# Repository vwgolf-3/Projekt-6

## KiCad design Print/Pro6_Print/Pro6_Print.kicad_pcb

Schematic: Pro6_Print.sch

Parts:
H1, H2, H3, H4: MountingHole_Pad; MountingHole_5.3mm_M5_DIN965_Pad

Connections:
GND: H1.1, H2.1, H3.1, H4.1; also elsewhere on the board

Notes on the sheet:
Motor etc
Endschalter
ESP32
RFID
Pumpen
Speisungen
Mikrocontroller
Durchflusssensoren
LED

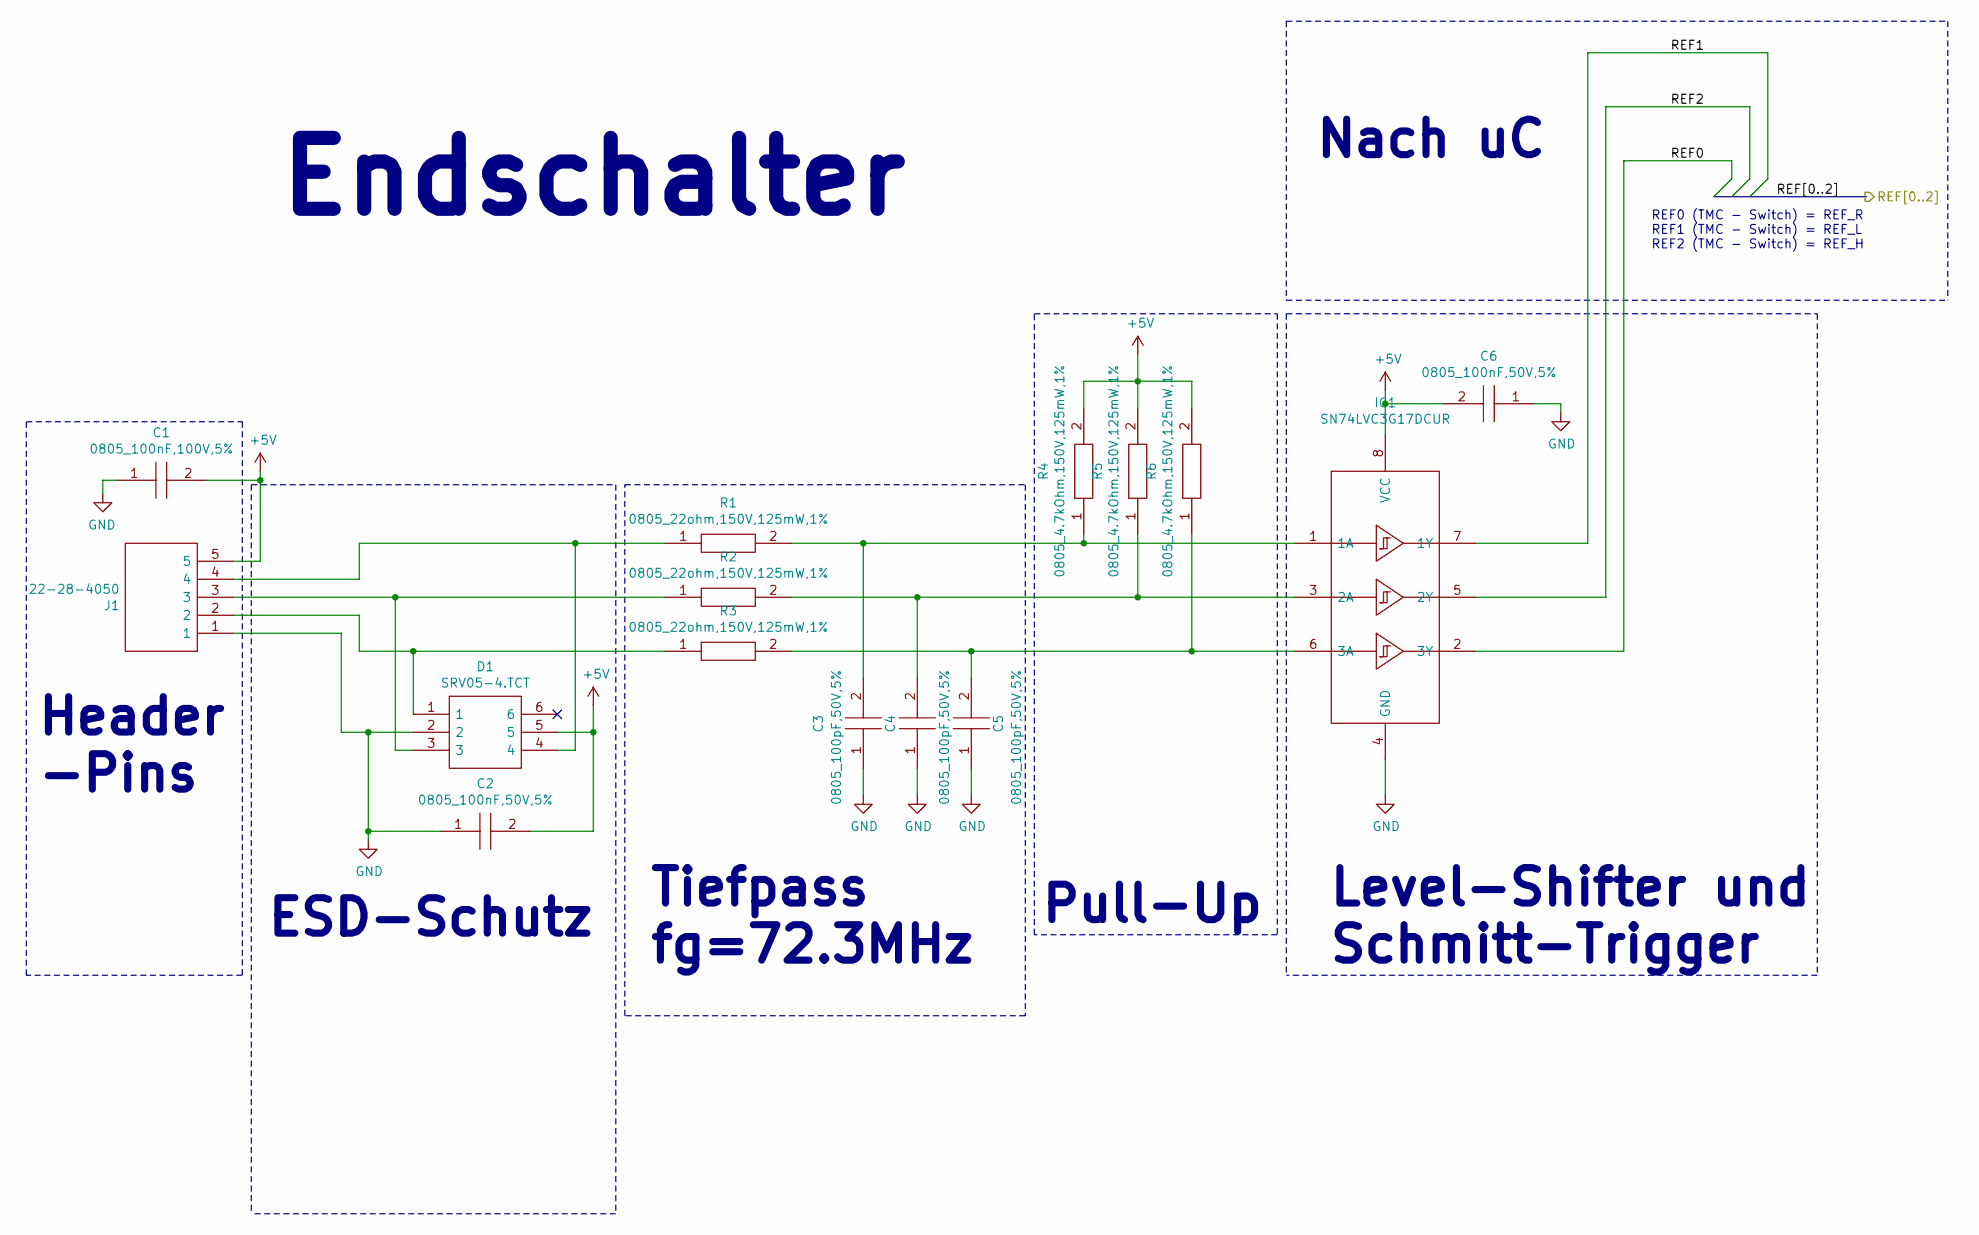
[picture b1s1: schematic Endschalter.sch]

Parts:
C1: 0805_100nF,100V,5%; CAPC2012X140N; Mouser Part Number 581-08051C104JAT2A
C2, C6: 0805_100nF,50V,5%; CAPC2012X88N; Mouser Part Number 80-C0805C104J5R
C3, C4, C5: 0805_100pF,50V,5%; CAPC2013X70N; Mouser Part Number 603-CC805JRNPO9BN101
D1: SRV05-4.TCT; SOT95P280X145-6N; Mouser Part Number 947-SRV05-4.TCT
IC1: SN74LVC3G17DCUR; SOP50P310X90-8N; Mouser Part Number 595-SN74LVC3G17DCUR
J1: 22-28-4050; HDRV5W66P0X254_1X5_1270X249X838P; Mouser Part Number 538-22-28-4050
R1, R2, R3: 0805_22ohm,150V,125mW,1%; RESC2012X70N; Mouser Part Number 667-ERJ-6ENF22R0V
R4, R5, R6: 0805_4.7kOhm,150V,125mW,1%; RESC2012X70N; Mouser Part Number 667-ERJ-6ENF4701V

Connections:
+5V: C1.2, C2.2, C6.2, D1.5, IC1.8 (VCC), J1.5, R4.2, R5.2, R6.2; also elsewhere on the board
/Atmega2560/REF0: IC1.2 (3Y); also elsewhere on the board
/Atmega2560/REF1: IC1.7 (1Y); also elsewhere on the board
/Atmega2560/REF2: IC1.5 (2Y); also elsewhere on the board
GND: C1.1, C2.1, C3.1, C4.1, C5.1, C6.1, D1.2, IC1.4 (GND), J1.1; also elsewhere on the board
unnamed: C3.2, IC1.1 (1A), R1.2, R4.1
unnamed: C4.2, IC1.3 (2A), R2.2, R5.1
unnamed: C5.2, IC1.6 (3A), R3.2, R6.1
unnamed: D1.1, J1.2, R3.1
unnamed: D1.3, J1.3, R2.1
unnamed: D1.4, J1.4, R1.1

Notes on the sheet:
Endschalter
REF0 (TMC - Switch) = REF_R REF1 (TMC - Switch) = REF_L REF2 (TMC - Switch) = REF_H
ESD-Schutz
Tiefpass fg=72.3MHz
Pull-Up
Level-Shifter und Schmitt-Trigger
Nach uC
Header -Pins

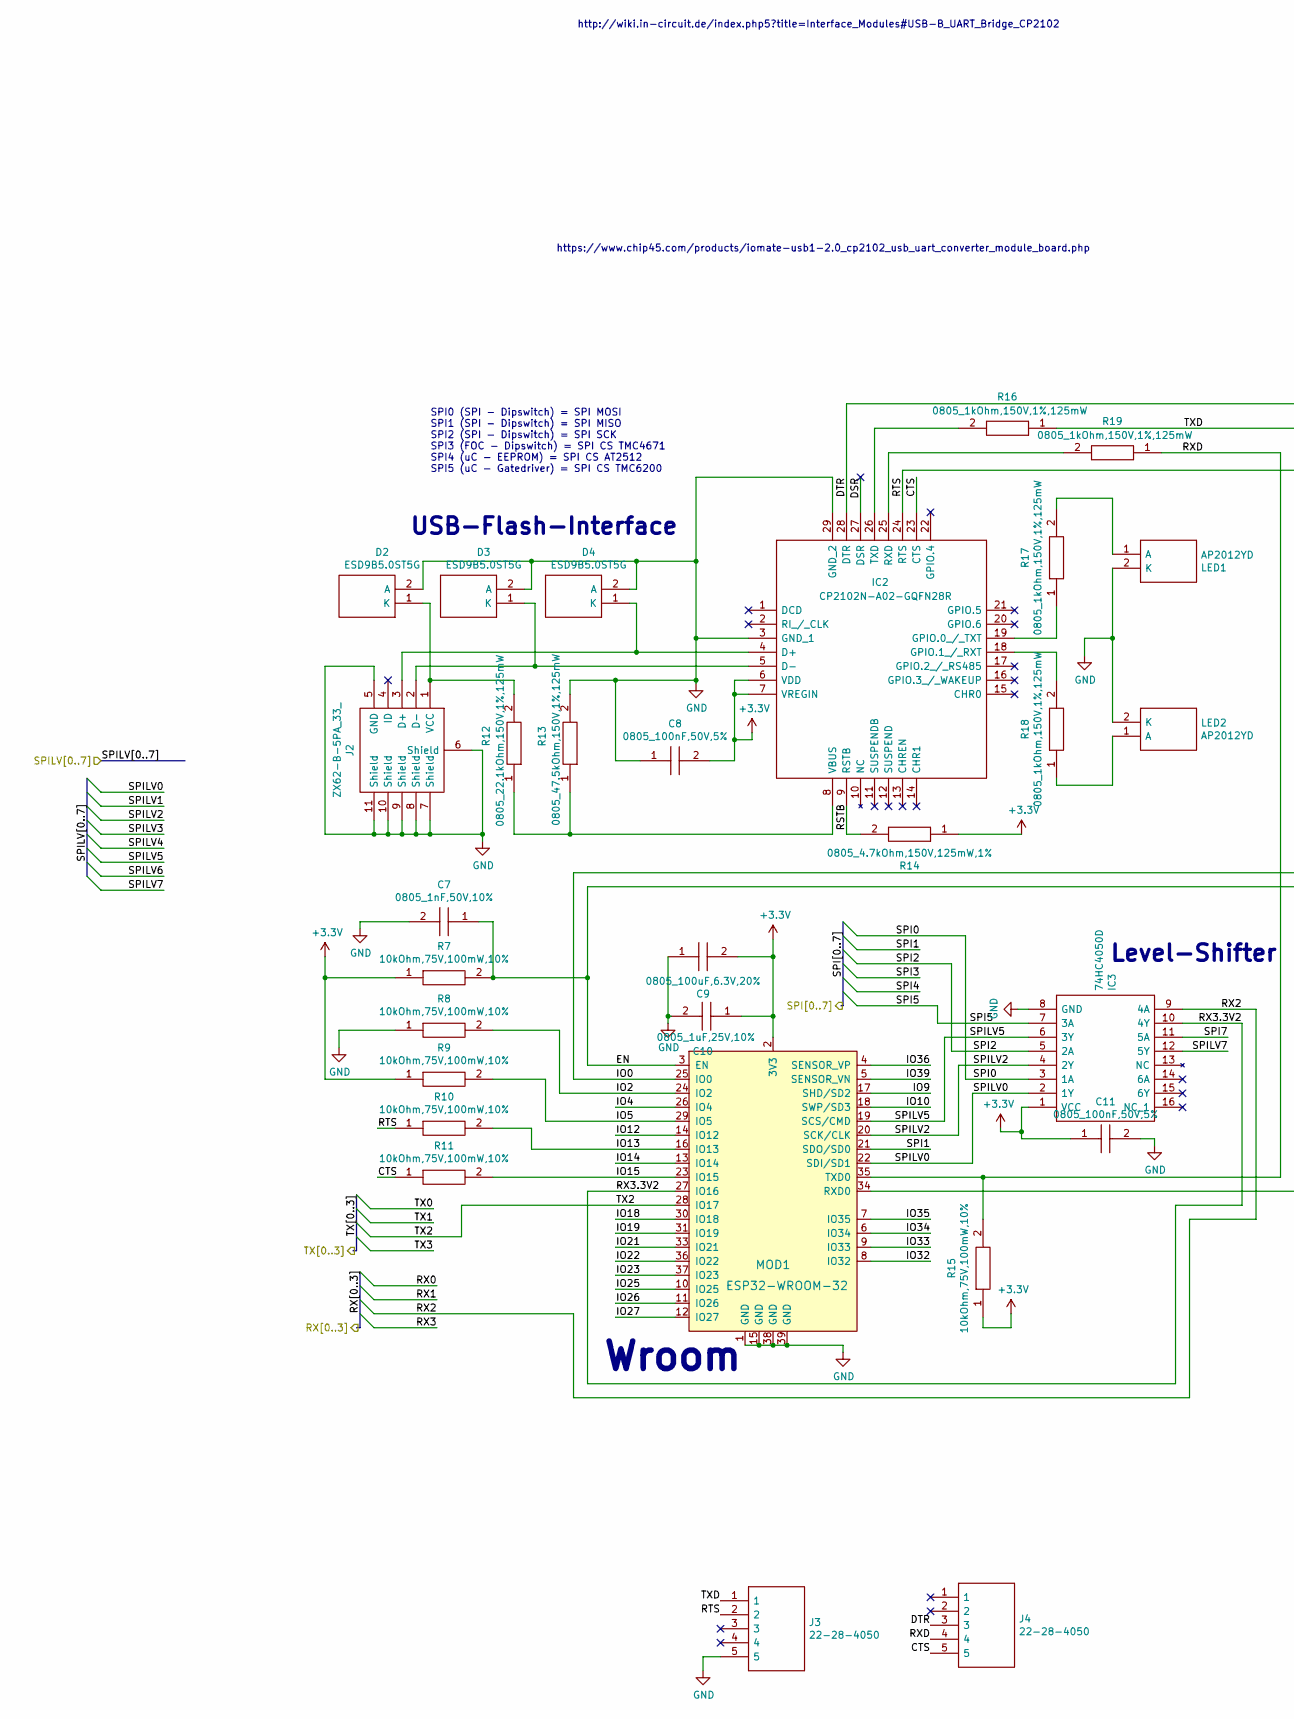
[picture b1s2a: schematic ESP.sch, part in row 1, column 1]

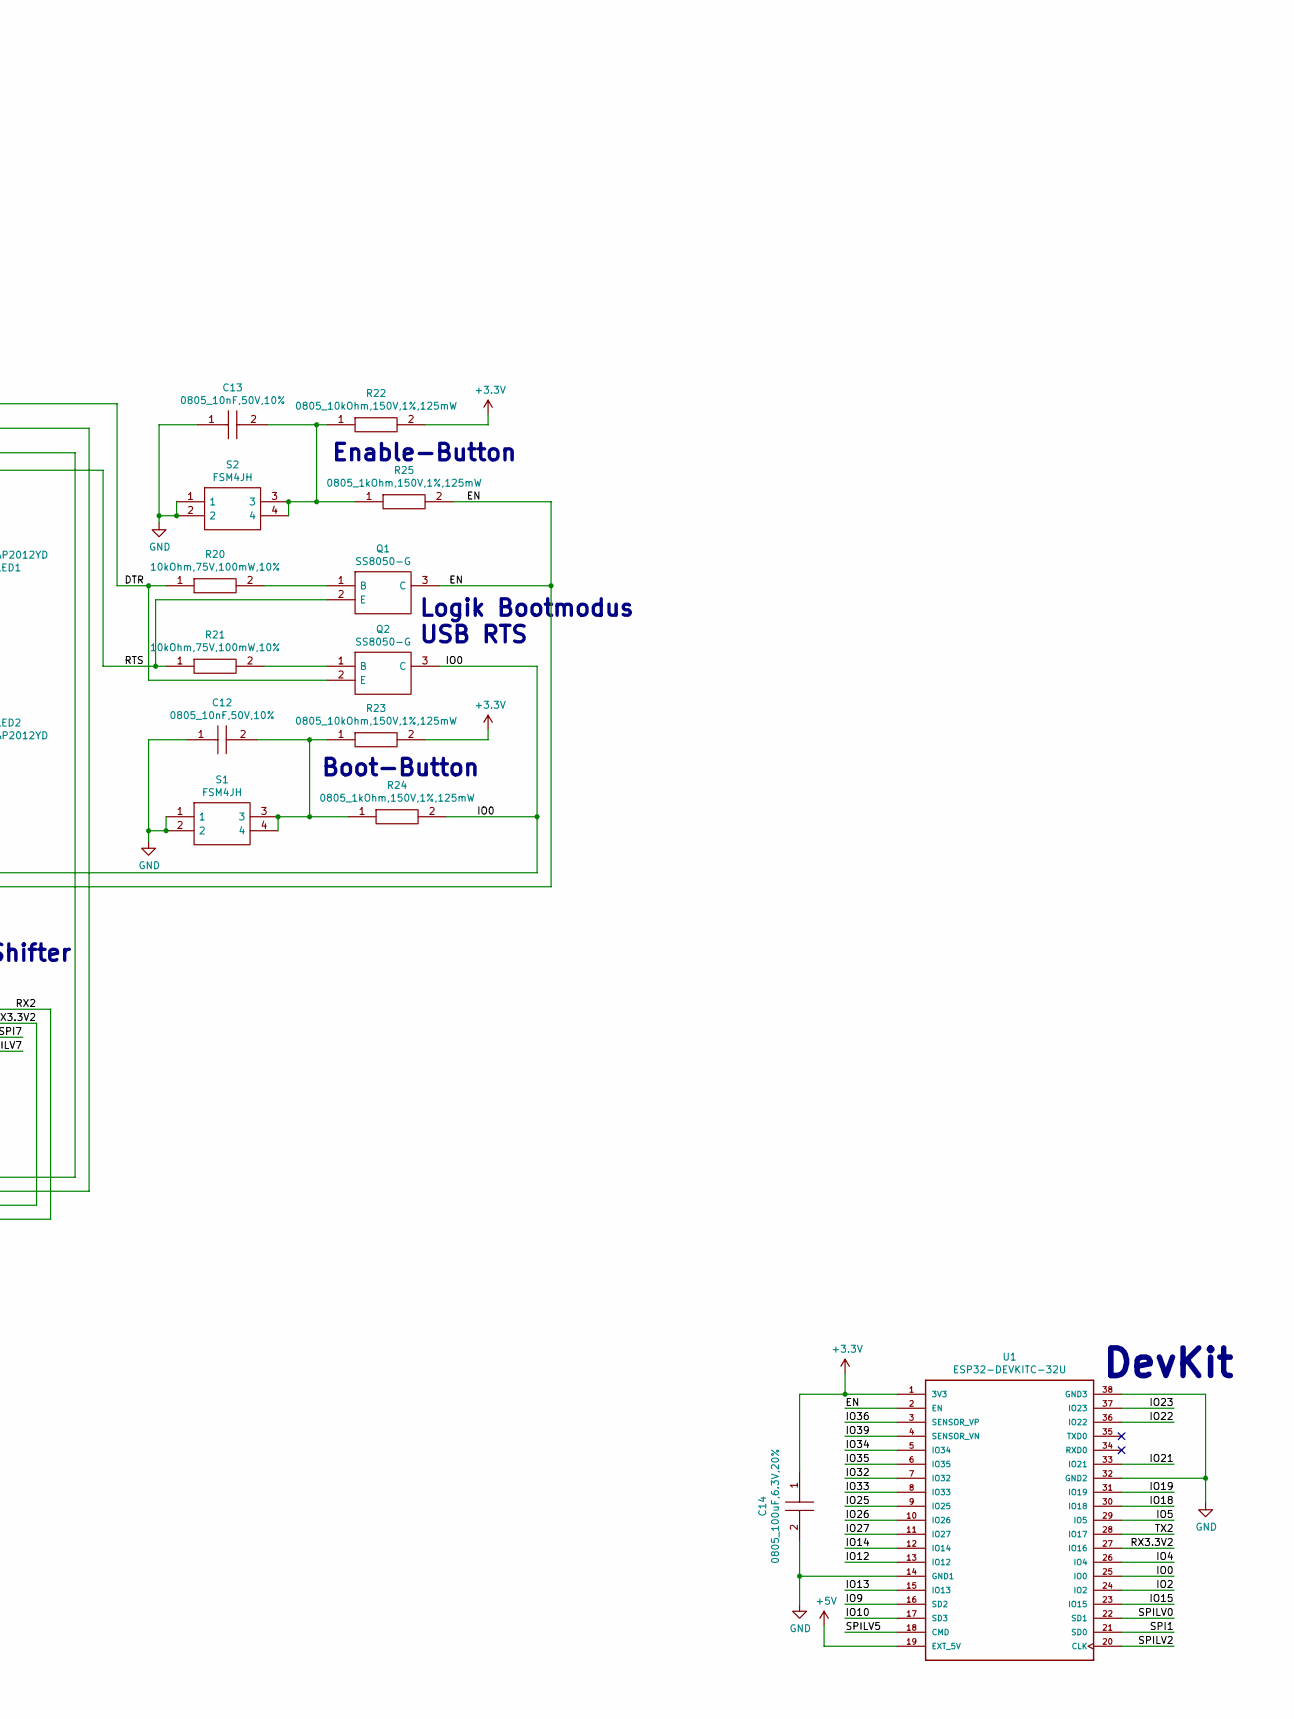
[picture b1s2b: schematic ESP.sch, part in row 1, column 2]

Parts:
C7: 0805_1nF,50V,10%; CAPC2012X90N; Mouser Part Number 710-885012207086
C8, C11: 0805_100nF,50V,5%; CAPC2012X88N; Mouser Part Number 80-C0805C104J5R
C9, C14: 0805_100uF,6.3V,20%; CAPC2012X145N; Mouser Part Number 81-GRM21BR60J107ME5K
C10: 0805_1uF,25V,10%; CAPC2013X140N; Mouser Part Number 80-C0805C105K3R
C12, C13: 0805_10nF,50V,10%; CAPC2012X90N; Mouser Part Number 710-885012207092
D2, D3, D4: ESD9B5.0ST5G; SODFL1006X40N; Mouser Part Number 863-ESD9B5.0ST5G
IC2: CP2102N-A02-GQFN28R; QFN50P500X500X80-29N-D; Mouser Part Number 634-CP2102NA02QFN28R
IC3: 74HC4050D; SOIC127P600X175-16N; Mouser Part Number 771-74HC4050D
J2: ZX62-B-5PA_33_; ZX62B5PA33; Mouser Part Number 798-ZX62-B-5PA33
J3, J4: 22-28-4050; HDRV5W66P0X254_1X5_1270X249X838P; Mouser Part Number 538-22-28-4050
LED1, LED2: AP2012YD; Mouser Part Number 604-AP2012YD
MOD1: ESP32-WROOM-32; ESP32-WROOM-32D; MPN ESP32-WROOM-32; Digi-Key_PN 1904-1010-1-ND
Q1, Q2: SS8050-G; SOT95P240X115-3N; Mouser Part Number 750-SS8050-G
R7, R8, R9, R10, R11, R15, R20, R21: 10kOhm,75V,100mW,10%; RESC1608X50N; Mouser Part Number 71-CRCW0603-10K-E3
R12: 0805_22.1kOhm,150V,1%,125mW; RESC2012X70N; Mouser Part Number 667-ERJ-6ENF2212V
R13: 0805_47.5kOhm,150V,1%,125mW; RESC2012X50N; Mouser Part Number 71-CRCW0805-47.5K-E3
R14: 0805_4.7kOhm,150V,125mW,1%; RESC2012X70N; Mouser Part Number 667-ERJ-6ENF4701V
R16, R17, R18, R19, R24, R25: 0805_1kOhm,150V,1%,125mW; RESC2012X60N; Mouser Part Number 71-CRCW08051K00FKEAC
R22, R23: 0805_10kOhm,150V,1%,125mW; RESC2012X60N; Mouser Part Number 71-CRCW080510K0FKEAC
S1, S2: FSM4JH; Mouser Part Number 506-FSM4JH
U1: ESP32-DEVKITC-32U; MODULE_ESP32-DEVKITC-32U

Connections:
+3V3: C8.2, C9.2, C10.1, C11.1, C14.1, IC2.6 (VDD), IC2.7 (VREGIN), IC3.1 (VCC), MOD1.2 (3V3), R7.1, R9.1, R14.1, R15.1, R22.2, R23.2, U1.1 (3V3); also elsewhere on the board
+5V: U1.19 (EXT_5V); also elsewhere on the board
/Atmega2560/RX2: IC3.9 (4A); also elsewhere on the board
/Atmega2560/SPI0: IC3.3 (1A); also elsewhere on the board
/Atmega2560/SPI1: MOD1.21 (SDO/SD0), U1.21 (SD0); also elsewhere on the board
/Atmega2560/SPI2: IC3.5 (2A); also elsewhere on the board
/Atmega2560/SPI5: IC3.7 (3A); also elsewhere on the board
/Atmega2560/SPI7: IC3.11 (5A); also elsewhere on the board
/Atmega2560/SPILV0: IC3.2 (1Y), MOD1.22 (SDI/SD1), U1.22 (SD1); also elsewhere on the board
/Atmega2560/SPILV2: IC3.4 (2Y), MOD1.20 (SCK/CLK), U1.20 (CLK); also elsewhere on the board
/Atmega2560/SPILV5: IC3.6 (3Y), MOD1.19 (SCS/CMD), U1.18 (CMD)
/Atmega2560/SPILV7: IC3.12 (5Y); also elsewhere on the board
/Atmega2560/TX2: MOD1.28 (IO17), U1.28 (IO17); also elsewhere on the board
/ESP/CTS: IC2.23 (CTS), J4.5, R11.1
/ESP/DTR: IC2.28 (DTR), J4.3, Q2.2 (E), R20.1
/ESP/EN: C7.1, MOD1.3 (EN), Q1.3 (C), R7.2, R25.2, U1.2 (EN)
/ESP/IO0: MOD1.25 (IO0), Q2.3 (C), R24.2, U1.25 (IO0)
/ESP/IO2: MOD1.24 (IO2), R8.2, U1.24 (IO2)
/ESP/IO4: MOD1.26 (IO4), U1.26 (IO4)
/ESP/IO5: MOD1.29 (IO5), R9.2, U1.29 (IO5)
/ESP/IO9: MOD1.17 (SHD/SD2), U1.16 (SD2)
/ESP/IO10: MOD1.18 (SWP/SD3), U1.17 (SD3)
/ESP/IO12: MOD1.14 (IO12), U1.13 (IO12)
/ESP/IO13: MOD1.16 (IO13), R10.2, U1.15 (IO13)
/ESP/IO14: MOD1.13 (IO14), U1.12 (IO14)
/ESP/IO15: MOD1.23 (IO15), R11.2, U1.23 (IO15)
/ESP/IO18: MOD1.30 (IO18), U1.30 (IO18)
/ESP/IO19: MOD1.31 (IO19), U1.31 (IO19)
/ESP/IO21: MOD1.33 (IO21), U1.33 (IO21)
/ESP/IO22: MOD1.36 (IO22), U1.36 (IO22)
/ESP/IO23: MOD1.37 (IO23), U1.37 (IO23)
/ESP/IO25: MOD1.10 (IO25), U1.9 (IO25)
/ESP/IO26: MOD1.11 (IO26), U1.10 (IO26)
/ESP/IO27: MOD1.12 (IO27), U1.11 (IO27)
/ESP/IO32: MOD1.8 (IO32), U1.7 (IO32)
/ESP/IO33: MOD1.9 (IO33), U1.8 (IO33)
/ESP/IO34: MOD1.6 (IO34), U1.5 (IO34)
/ESP/IO35: MOD1.7 (IO35), U1.6 (IO35)
/ESP/IO36: MOD1.4 (SENSOR_VP), U1.3 (SENSOR_VP)
/ESP/IO39: MOD1.5 (SENSOR_VN), U1.4 (SENSOR_VN)
/ESP/RSTB: IC2.9 (RSTB), R14.2
/ESP/RTS: IC2.24 (RTS), J3.2, Q1.2 (E), R10.1, R21.1
/ESP/RX3.3V2: IC3.10 (4Y), MOD1.27 (IO16), U1.27 (IO16)
/ESP/RXD: J4.4, MOD1.35 (TXD0), R15.2, R19.1
/ESP/TXD: J3.1, MOD1.34 (RXD0), R16.1
GND: C7.2, C8.1, C9.1, C10.2, C11.2, C12.1, C13.1, C14.2, D2.2 (A), D3.2 (A), D4.2 (A), IC2.3 (GND_1), IC2.29 (GND_2), IC3.8 (GND), J2.5 (GND), J2.6 (Shield), J2.7 (Shield), J2.8 (Shield), J2.9 (Shield), J2.10 (Shield), J2.11 (Shield), J3.5, LED1.2 (K), LED2.2 (K), MOD1.1 (GND), MOD1.15 (GND), MOD1.38 (GND), MOD1.39 (GND), R8.1, R13.2, S1.1, S1.2, S2.1, S2.2, U1.14 (GND1), U1.32 (GND2), U1.38 (GND3); also elsewhere on the board
unnamed: C12.2, R23.1, R24.1, S1.3, S1.4
unnamed: C13.2, R22.1, R25.1, S2.3, S2.4
unnamed: D2.1 (K), J2.1 (VCC), R12.2
unnamed: D3.1 (K), IC2.5 (D-), J2.2 (D-)
unnamed: D4.1 (K), IC2.4 (D+), J2.3 (D+)
unnamed: IC2.8 (VBUS), R12.1, R13.1
unnamed: IC2.18 (GPIO.1_/_RXT), R18.2
unnamed: IC2.19 (GPIO.0_/_TXT), R17.1
unnamed: IC2.25 (RXD), R19.2
unnamed: IC2.26 (TXD), R16.2
unnamed: LED1.1 (A), R17.2
unnamed: LED2.1 (A), R18.1
unnamed: Q1.1 (B), R20.2
unnamed: Q2.1 (B), R21.2

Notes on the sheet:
USB-Flash-Interface
SPI0 (SPI - Dipswitch) = SPI MOSI SPI1 (SPI - Dipswitch) = SPI MISO SPI2 (SPI - Dipswitch) = SPI SCK SPI3 (FOC - Dipswitch) = SPI CS TMC4671 SPI4 (uC - EEPROM) = SPI CS AT2512 SPI5 (uC - Gatedriver) = SPI CS TMC6200
Enable-Button
Boot-Button
Logik Bootmodus USB RTS
Level-Shifter
Wroom
DevKit
https://www.chip45.com/products/iomate-usb1-2.0_cp2102_usb_uart_converter_module_board.php
http://wiki.in-circuit.de/index.php5?title=Interface_Modules#USB-B_UART_Bridge_CP2102

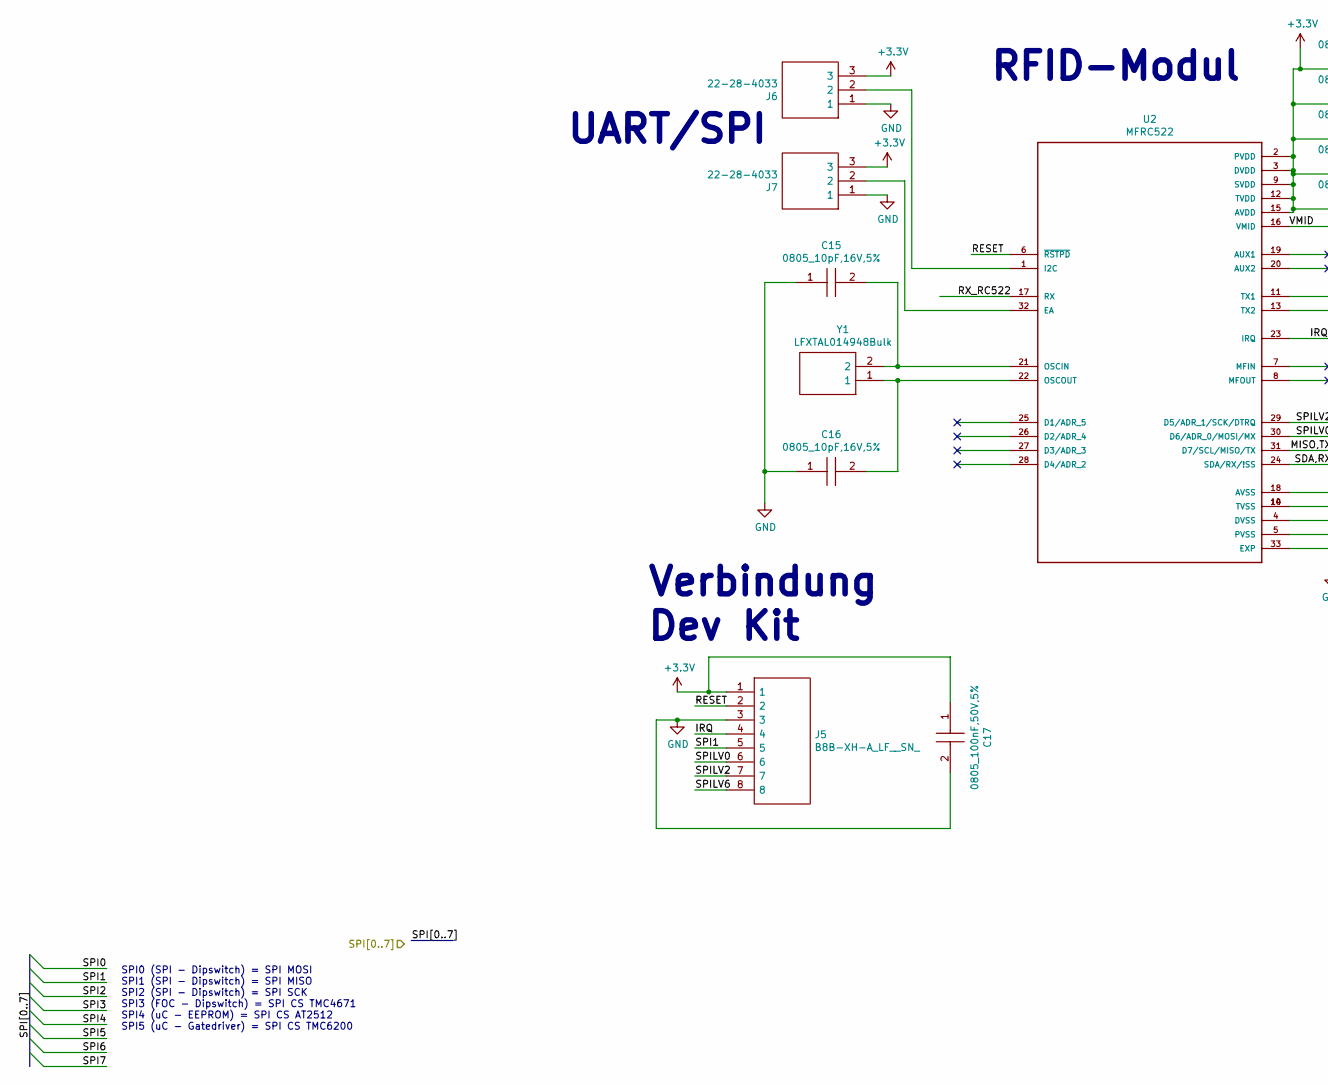
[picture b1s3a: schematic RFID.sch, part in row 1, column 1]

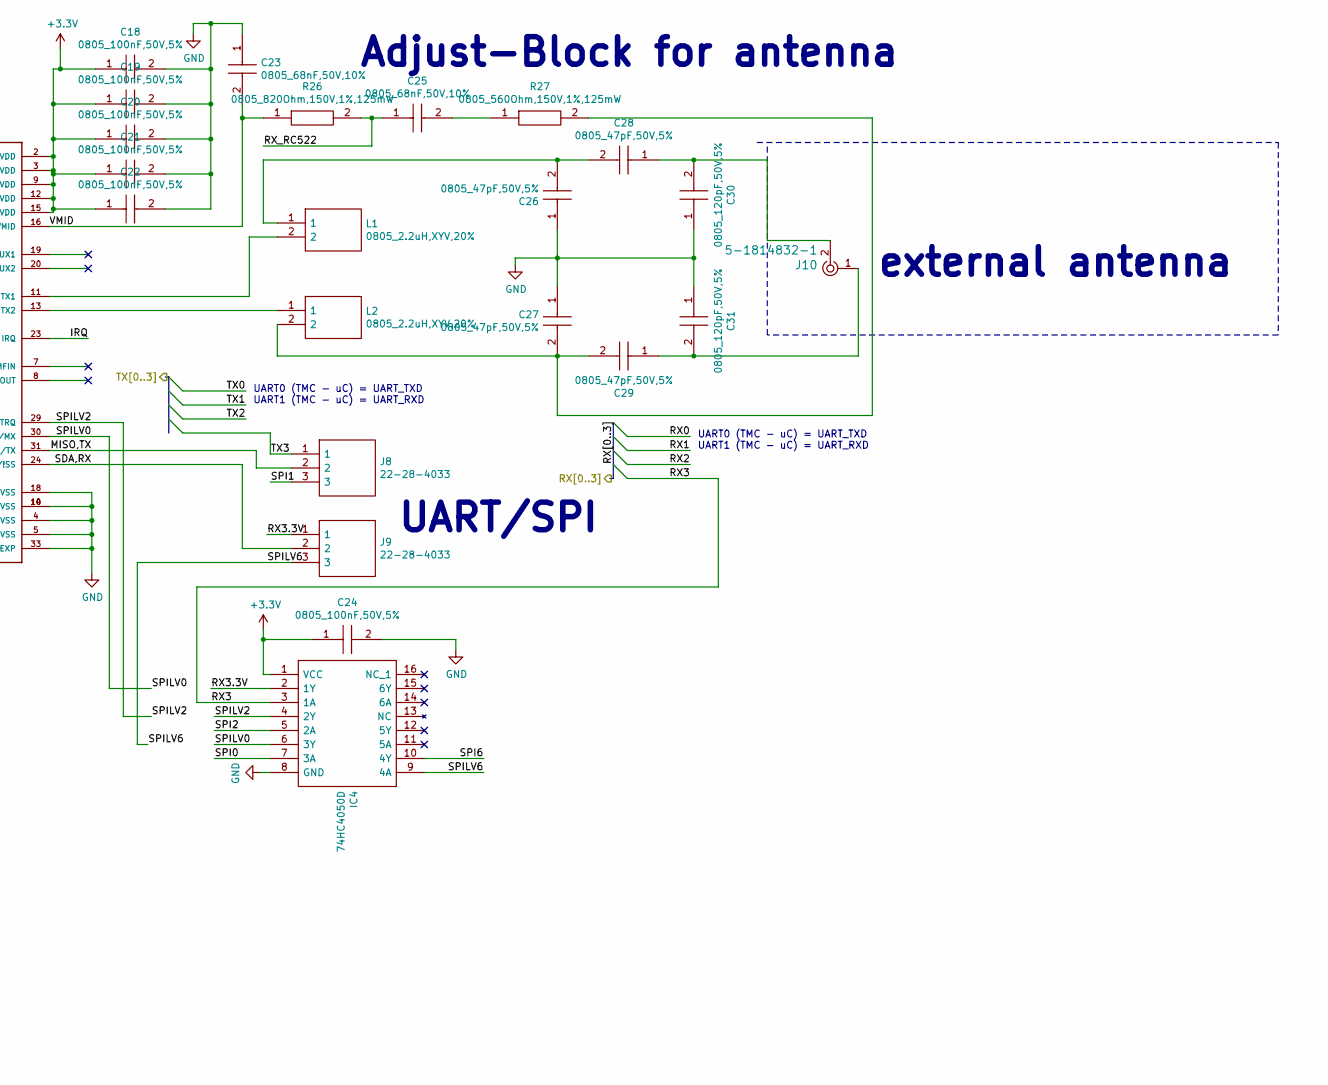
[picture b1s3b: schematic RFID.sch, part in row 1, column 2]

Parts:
C15, C16: 0805_10pF,16V,5%; CAPC2012X70N; Mouser Part Number 710-885012007010
C17, C18, C19, C20, C21, C22, C24: 0805_100nF,50V,5%; CAPC2012X88N; Mouser Part Number 80-C0805C104J5R
C23, C25: 0805_68nF,50V,10%; CAPC2012X90N; Mouser Part Number 710-885012207097
C26, C27, C28, C29: 0805_47pF,50V,5%; CAPC2013X88N; Mouser Part Number 80-C0805C470J5G
C30, C31: 0805_120pF,50V,5%; CAPC2012X70N; Mouser Part Number 81-GRM212C1H121JA01D
IC4: 74HC4050D; SOIC127P600X175-16N; Mouser Part Number 771-74HC4050D
J5: B8B-XH-A_LF__SN_; HDRV8W64P0X250_1X8_2240X575X700P; Manufacturer_Part_Number B8B-XH-A(LF)(SN)
J6, J7, J8, J9: 22-28-4033; HDRV3W66P0X254_1X3_762X249X838P; Mouser Part Number 538-22-28-4033
J10: 5-1814832-1; RF_SMA_Vertical_5-1814832-1; MPN 5-1814832-1; Digi-Key_PN A97594-ND
L1, L2: 0805_2.2uH,XYV,20%; INDC2012X105N; Mouser Part Number 810-MLZ2012A2R2WT000
R26: 0805_820Ohm,150V,1%,125mW; RESC2012X60N; Mouser Part Number 652-CR0805FX-8200ELF
R27: 0805_560Ohm,150V,1%,125mW; RESC2012X50N; Mouser Part Number 71-CRCW0805-560-E3
U2: MFRC522; QFN50P500X500X100-33N
Y1: LFXTAL014948Bulk; Mouser Part Number 449-LFXTAL014948BULK

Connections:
+3V3: C17.1, C18.1, C19.1, C20.1, C21.1, C22.1, C24.1, IC4.1 (VCC), J5.1, J6.3, J7.3, U2.2 (PVDD), U2.3 (DVDD), U2.9 (SVDD), U2.12 (TVDD), U2.15 (AVDD); also elsewhere on the board
/Atmega2560/RX3: IC4.3 (1A); also elsewhere on the board
/Atmega2560/SPI0: IC4.7 (3A); also elsewhere on the board
/Atmega2560/SPI1: J5.5, J8.3; also elsewhere on the board
/Atmega2560/SPI2: IC4.5 (2A); also elsewhere on the board
/Atmega2560/SPI6: IC4.10 (4Y); also elsewhere on the board
/Atmega2560/TX3: J8.1; also elsewhere on the board
/RFID/IRQ: J5.4, U2.23 (IRQ)
/RFID/MISO,TX: J8.2, U2.31 (D7/SCL/MISO/TX)
/RFID/RESET: J5.2, U2.6 (~RSTPD~)
/RFID/RX3.3V: IC4.2 (1Y), J9.1
/RFID/RX_RC522: C25.1, R26.2, U2.17 (RX)
/RFID/SDA,RX: J9.2, U2.24 (SDA/RX/!SS)
/RFID/SPILV0: IC4.6 (3Y), J5.6, U2.30 (D6/ADR_0/MOSI/MX)
/RFID/SPILV2: IC4.4 (2Y), J5.7, U2.29 (D5/ADR_1/SCK/DTRQ)
/RFID/SPILV6: IC4.9 (4A), J5.8, J9.3
/RFID/VMID: C23.2, R26.1, U2.16 (VMID)
GND: C15.1, C16.1, C17.2, C18.2, C19.2, C20.2, C21.2, C22.2, C23.1, C24.2, C26.1, C27.1, C30.1, C31.1, IC4.8 (GND), J5.3, J6.1, J7.1, U2.4 (DVSS), U2.5 (PVSS), U2.10 (TVSS), U2.14 (TVSS), U2.18 (AVSS), U2.33 (EXP); also elsewhere on the board
unnamed: C15.2, U2.21 (OSCIN), Y1.2
unnamed: C16.2, U2.22 (OSCOUT), Y1.1
unnamed: C25.2, R27.1
unnamed: C26.2, C28.2, L1.1
unnamed: C27.2, C29.2, L2.2, R27.2
unnamed: C28.1, C30.2, J10.2
unnamed: C29.1, C31.2, J10.1
unnamed: J6.2, U2.1 (I2C)
unnamed: J7.2, U2.32 (EA)
unnamed: L1.2, U2.11 (TX1)
unnamed: L2.1, U2.13 (TX2)

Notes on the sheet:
Verbindung Dev Kit
SPI0 (SPI - Dipswitch) = SPI MOSI SPI1 (SPI - Dipswitch) = SPI MISO SPI2 (SPI - Dipswitch) = SPI SCK SPI3 (FOC - Dipswitch) = SPI CS TMC4671 SPI4 (uC - EEPROM) = SPI CS AT2512 SPI5 (uC - Gatedriver) = SPI CS TMC6200
RFID-Modul
UART/SPI
external antenna
Adjust-Block for antenna
UART0 (TMC - uC) = UART_TXD UART1 (TMC - uC) = UART_RXD

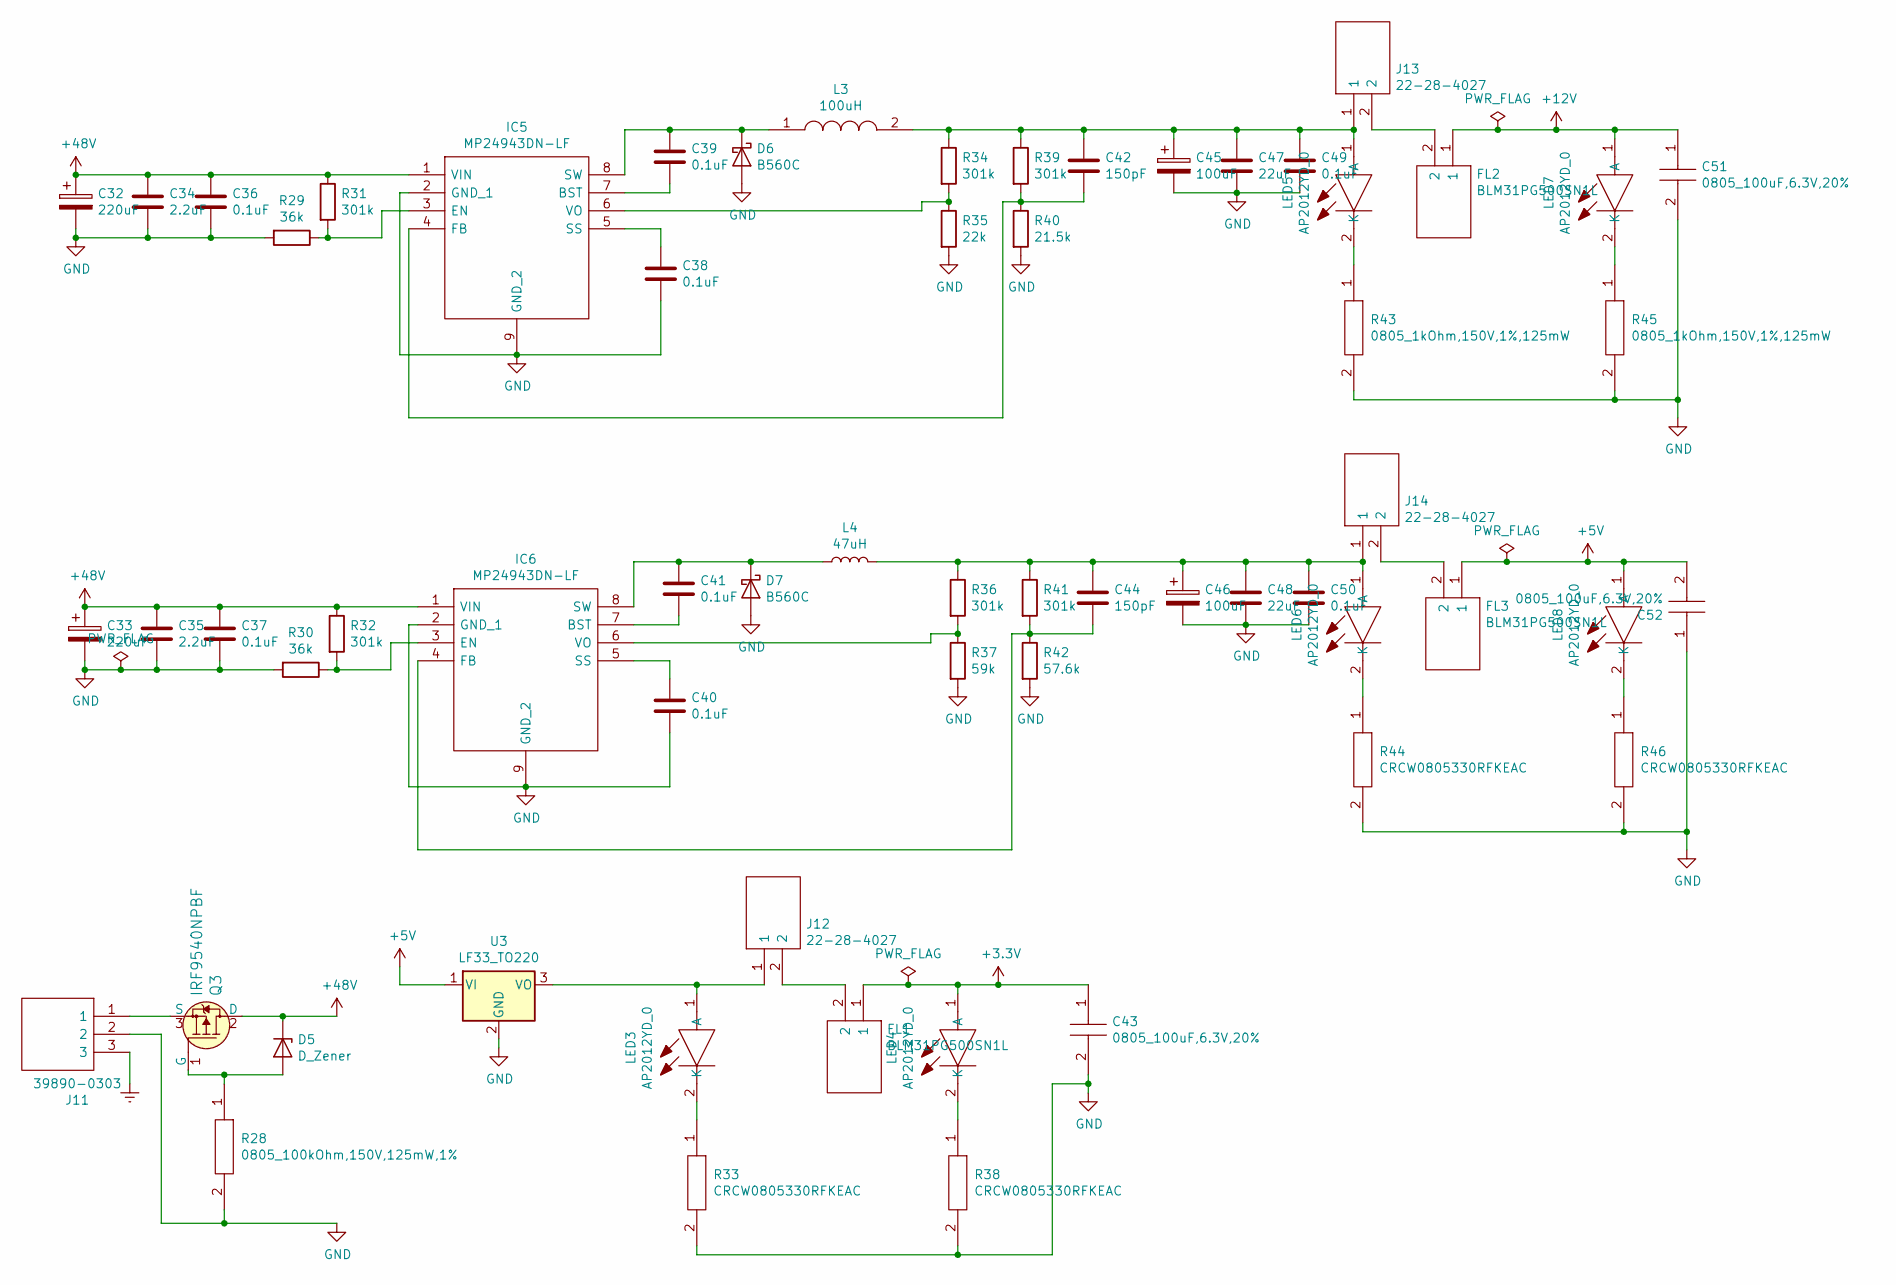
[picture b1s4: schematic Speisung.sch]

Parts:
C32, C33: 220uF; CP_Elec_10x7.9
C34, C35: 2.2uF; C_1206_3216Metric
C36, C37, C39, C41, C49, C50: 0.1uF; C_1206_3216Metric
C38, C40: 0.1uF; C_0805_2012Metric
C42, C44: 150pF; C_0805_2012Metric
C43, C51, C52: 0805_100uF,6.3V,20%; CAPC2012X145N; Mouser Part Number 81-GRM21BR60J107ME5K
C45, C46: 100uF; CP_Elec_6.3x7.7
C47, C48: 22uF; C_1206_3216Metric
D5: D_Zener; C_0805_2012Metric_Pad1.15x1.40mm_HandSolder
D6, D7: B560C; D_SMC
FL1, FL2, FL3: BLM31PG500SN1L; BEADC3216X130N; Mouser Part Number 81-BLM31P500S
IC5, IC6: MP24943DN-LF; SOIC127P600X170-9N; Manufacturer_Part_Number MP24943DN-LF; Mouser Part Number 946-MP24943DNLF
J11: 39890-0303; 398900303; Mouser Part Number 538-39890-0303
J12, J13, J14: 22-28-4027; HDRV2W66P0X254_1X2_508X249X1067P; Mouser Part Number 538-22-28-4027
L3: 100uH; INDPM150150X860N; Mouser Part Number 994-MSS1583-104KEB
L4: 47uH; L_12x12mm_H8mm
LED3, LED4, LED5, LED6, LED7, LED8: AP2012YD_0; AP2012YD; Mouser Part Number 604-AP2012YD
Q3: IRF9540NPBF; TO-220-3; MPN IRF9540NPBF; Digi-Key_PN IRF9540NPBF-ND
R28: 0805_100kOhm,150V,125mW,1%; RESC2012X60N; Mouser Part Number 71-CRCW0805100KFKEAC
R29, R30: 36k; R_0805_2012Metric
R31, R32, R34, R36, R39, R41: 301k; R_0805_2012Metric
R33, R38, R44, R46: CRCW0805330RFKEAC; RESC2012X60N; Mouser Part Number 71-CRCW0805330RFKEAC
R35: 22k; R_0805_2012Metric
R37: 59k; R_0805_2012Metric
R40: 21.5k; R_0805_2012Metric
R42: 57.6k; R_0805_2012Metric
R43, R45: 0805_1kOhm,150V,1%,125mW; RESC2012X60N; Mouser Part Number 71-CRCW08051K00FKEAC
U3: LF33_TO220; TO-252-2

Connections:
+3V3: C43.1, FL1.1, LED4.1 (A); also elsewhere on the board
+5V: C52.2, FL3.1, LED8.1 (A), U3.1 (VI); also elsewhere on the board
+12V: C51.1, FL2.1, LED7.1 (A); also elsewhere on the board
+48V: C32.1, C33.1, C34.1, C35.1, C36.1, C37.1, D5.1 (K), IC5.1 (VIN), IC6.1 (VIN), Q3.2 (D), R31.1, R32.1; also elsewhere on the board
Earth: J11.3; also elsewhere on the board
GND: C32.2, C33.2, C34.2, C35.2, C36.2, C37.2, C38.2, C40.2, C43.2, C45.2, C46.2, C47.2, C48.2, C49.2, C50.2, C51.2, C52.1, D6.2 (A), D7.2 (A), IC5.2 (GND_1), IC5.9 (GND_2), IC6.2 (GND_1), IC6.9 (GND_2), J11.2, R28.2, R29.2, R30.2, R33.2, R35.2, R37.2, R38.2, R40.2, R42.2, R43.2, R44.2, R45.2, R46.2, U3.2 (GND); also elsewhere on the board
unnamed: C38.1, IC5.5 (SS)
unnamed: C39.1, D6.1 (K), IC5.8 (SW), L3.1
unnamed: C39.2, IC5.7 (BST)
unnamed: C40.1, IC6.5 (SS)
unnamed: C41.1, D7.1 (K), IC6.8 (SW), L4.1
unnamed: C41.2, IC6.7 (BST)
unnamed: C42.1, C45.1, C47.1, C49.1, J13.1, L3.2, LED5.1 (A), R34.1, R39.1
unnamed: C42.2, IC5.4 (FB), R39.2, R40.1
unnamed: C44.1, C46.1, C48.1, C50.1, J14.1, L4.2, LED6.1 (A), R36.1, R41.1
unnamed: C44.2, IC6.4 (FB), R41.2, R42.1
unnamed: D5.2 (A), Q3.1 (G), R28.1
unnamed: FL1.2, J12.2
unnamed: FL2.2, J13.2
unnamed: FL3.2, J14.2
unnamed: IC5.3 (EN), R29.1, R31.2
unnamed: IC5.6 (VO), R34.2, R35.1
unnamed: IC6.3 (EN), R30.1, R32.2
unnamed: IC6.6 (VO), R36.2, R37.1
unnamed: J11.1, Q3.3 (S)
unnamed: J12.1, LED3.1 (A), U3.3 (VO)
unnamed: LED3.2 (K), R33.1
unnamed: LED4.2 (K), R38.1
unnamed: LED5.2 (K), R43.1
unnamed: LED6.2 (K), R44.1
unnamed: LED7.2 (K), R45.1
unnamed: LED8.2 (K), R46.1
